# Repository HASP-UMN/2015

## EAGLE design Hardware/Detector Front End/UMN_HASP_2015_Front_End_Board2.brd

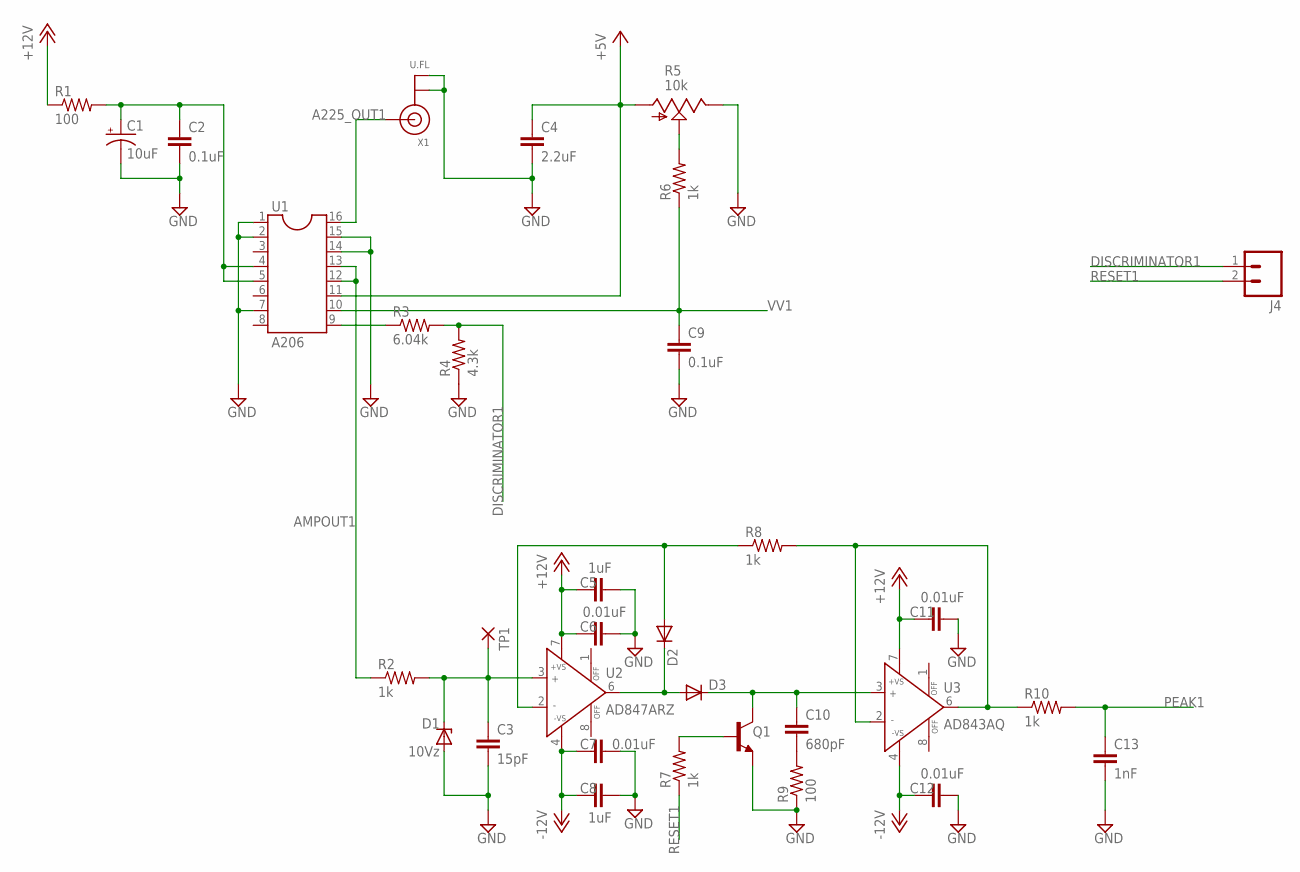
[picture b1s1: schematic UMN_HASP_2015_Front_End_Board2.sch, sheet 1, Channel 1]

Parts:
C1: 10uF; C/6032-28R
C2, C9: 0.1uF; C0603K
C3: 15pF; C0402K
C4: 2.2uF; C0603K
C5, C8: 1uF; C0603K
C6, C7, C11, C12: 0.01uF; C0402K
C10: 680pF; C0402K
C13: 1nF; C0402K
D1: 10Vz; SOT23
D2, D3: DIODE-SOD323-R; SOD323-R
J4: M02PTH; 1X02
Q1: -NPN-SOT23-EBC; SOT23-EBC
R1, R9: 100; R0603
R2, R6, R7, R8: 1k; R0603
R3: 6.04k; R0603
R4: 4.3k; R0603
R5: 10k; 3223J
R10: 1k; R0402
TP1: SMD2; SMD1,27-2,54
U1: A206; SOCKET-16
U2: AD847ARZ; SO8
U3: AD843AQ; DIL08
X1: U.FL

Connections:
+5V: C4.1, R5.1 (A), U1.11; also elsewhere on the board
+12V: C5.1, C6.1, C11.1, R1.1, U2.7 (+VS), U3.7 (+VS); also elsewhere on the board
-12V: C7.1, C8.1, C12.1, U2.4 (-VS), U3.4 (-VS); also elsewhere on the board
A225_OUT1: U1.16, X1.3 (SIGNAL)
AMPOUT1: R2.1, U1.12, U1.13
DISCRIMINATOR1: J4.1, R3.2, R4.2
GND: C1.-, C2.2, C3.2, C4.2, C5.2, C6.2, C7.2, C8.2, C9.2, C11.2, C12.2, C13.2, D1.1 (A), Q1.E, R4.1, R5.3 (E), R9.1, U1.1, U1.2, U1.7, U1.14, U1.15, X1.1 (GND), X1.2 (GND); also elsewhere on the board
unnamed: C1.+, C2.1, R1.2, U1.4, U1.5
unnamed: C3.1, D1.3 (C), R2.2, TP1.1, U2.3 (IN+)
unnamed: R3.1, U1.9
unnamed: D2.C, D3.A, U2.6 (OUT)
unnamed: R5.2 (S), R6.2
unnamed: D2.A, R8.1, U2.2 (IN-)
unnamed: C10.1, D3.C, Q1.C, U3.3 (IN+)
unnamed: C10.2, R9.2
unnamed: Q1.B, R7.2
unnamed: R8.2, R10.1, U3.2 (IN-), U3.6 (OUT)
PEAK1: C13.1, R10.2; also elsewhere on the board
RESET1: J4.2, R7.1
VV1: C9.1, R6.1, U1.10

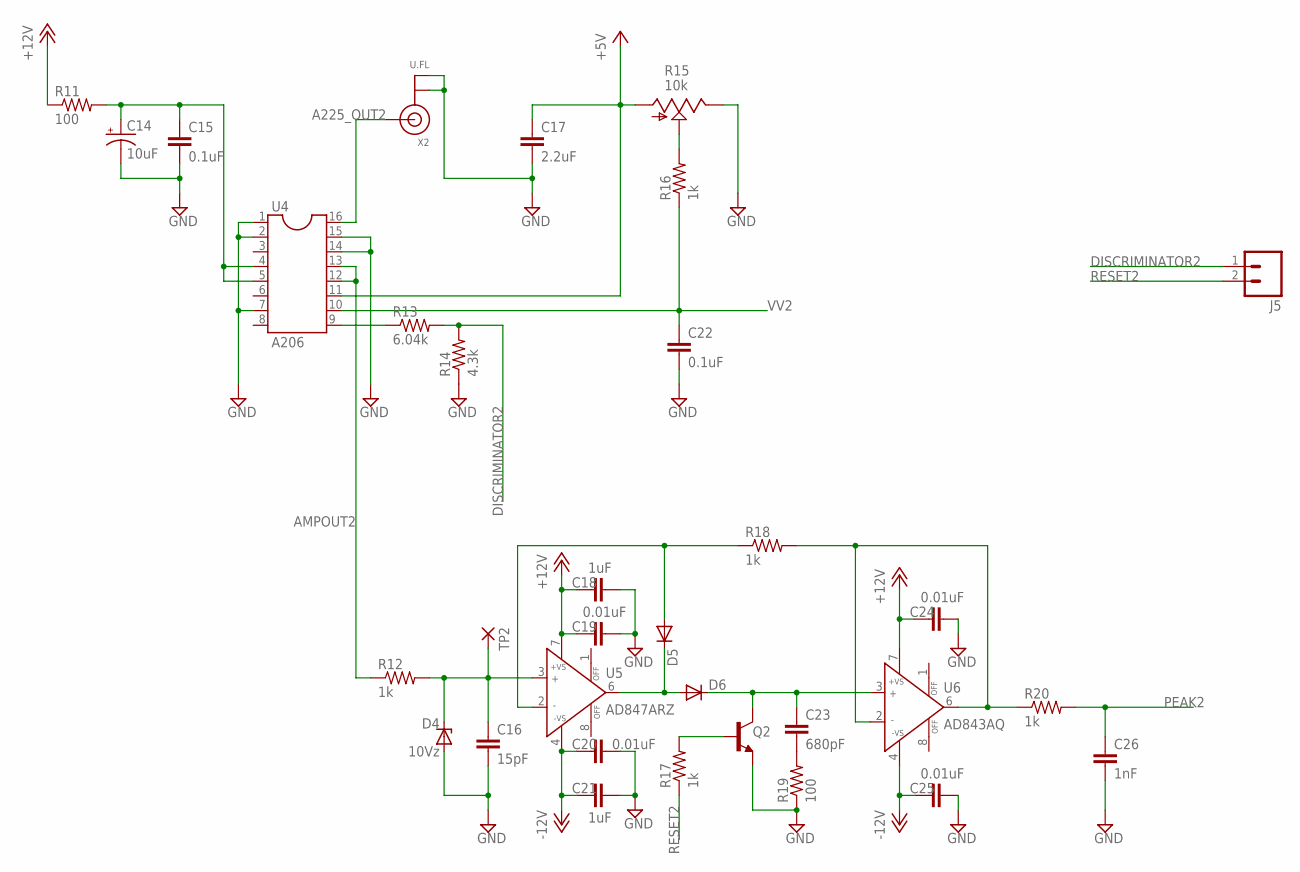
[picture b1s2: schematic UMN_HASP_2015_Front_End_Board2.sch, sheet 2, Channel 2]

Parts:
C14: 10uF; C/6032-28R
C15, C22: 0.1uF; C0603K
C16: 15pF; C0402K
C17: 2.2uF; C0603K
C18, C21: 1uF; C0603K
C19, C20, C24, C25: 0.01uF; C0402K
C23: 680pF; C0402K
C26: 1nF; C0402K
D4: 10Vz; SOT23
D5, D6: DIODE-SOD323-R; SOD323-R
J5: M02PTH; 1X02
Q2: -NPN-SOT23-EBC; SOT23-EBC
R11, R19: 100; R0603
R12, R16, R17, R18: 1k; R0603
R13: 6.04k; R0603
R14: 4.3k; R0603
R15: 10k; 3223J
R20: 1k; R0402
TP2: SMD2; SMD1,27-2,54
U4: A206; SOCKET-16
U5: AD847ARZ; SO8
U6: AD843AQ; DIL08
X2: U.FL

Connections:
+5V: C17.1, R15.1 (A), U4.11; also elsewhere on the board
+12V: C18.1, C19.1, C24.1, R11.1, U5.7 (+VS), U6.7 (+VS); also elsewhere on the board
-12V: C20.1, C21.1, C25.1, U5.4 (-VS), U6.4 (-VS); also elsewhere on the board
A225_OUT2: U4.16, X2.3 (SIGNAL)
AMPOUT2: R12.1, U4.12, U4.13
DISCRIMINATOR2: J5.1, R13.2, R14.2
GND: C14.-, C15.2, C16.2, C17.2, C18.2, C19.2, C20.2, C21.2, C22.2, C24.2, C25.2, C26.2, D4.1 (A), Q2.E, R14.1, R15.3 (E), R19.1, U4.1, U4.2, U4.7, U4.14, U4.15, X2.1 (GND), X2.2 (GND); also elsewhere on the board
unnamed: C14.+, C15.1, R11.2, U4.4, U4.5
unnamed: R13.1, U4.9
unnamed: R15.2 (S), R16.2
unnamed: C16.1, D4.3 (C), R12.2, TP2.1, U5.3 (IN+)
unnamed: D5.C, D6.A, U5.6 (OUT)
unnamed: D5.A, R18.1, U5.2 (IN-)
unnamed: C23.1, D6.C, Q2.C, U6.3 (IN+)
unnamed: C23.2, R19.2
unnamed: Q2.B, R17.2
unnamed: R18.2, R20.1, U6.2 (IN-), U6.6 (OUT)
PEAK2: C26.1, R20.2; also elsewhere on the board
RESET2: J5.2, R17.1
VV2: C22.1, R16.1, U4.10

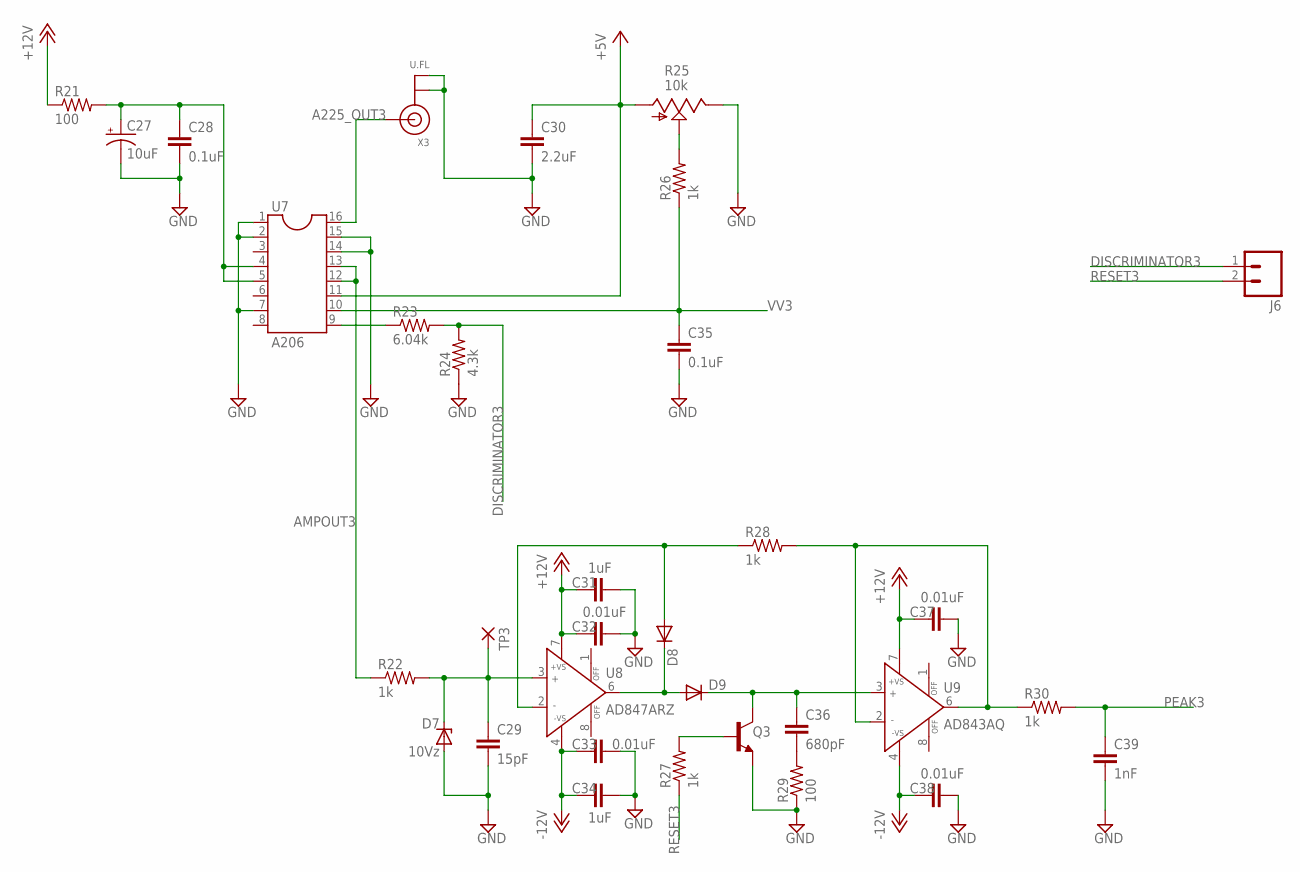
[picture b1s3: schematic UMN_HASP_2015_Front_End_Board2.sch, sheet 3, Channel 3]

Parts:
C27: 10uF; C/6032-28R
C28, C35: 0.1uF; C0603K
C29: 15pF; C0402K
C30: 2.2uF; C0603K
C31, C34: 1uF; C0603K
C32, C33, C37, C38: 0.01uF; C0402K
C36: 680pF; C0402K
C39: 1nF; C0402K
D7: 10Vz; SOT23
D8, D9: DIODE-SOD323-R; SOD323-R
J6: M02PTH; 1X02
Q3: -NPN-SOT23-EBC; SOT23-EBC
R21, R29: 100; R0603
R22, R26, R27, R28: 1k; R0603
R23: 6.04k; R0603
R24: 4.3k; R0603
R25: 10k; 3223J
R30: 1k; R0402
TP3: SMD2; SMD1,27-2,54
U7: A206; SOCKET-16
U8: AD847ARZ; SO8
U9: AD843AQ; DIL08
X3: U.FL

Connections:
+5V: C30.1, R25.1 (A), U7.11; also elsewhere on the board
+12V: C31.1, C32.1, C37.1, R21.1, U8.7 (+VS), U9.7 (+VS); also elsewhere on the board
-12V: C33.1, C34.1, C38.1, U8.4 (-VS), U9.4 (-VS); also elsewhere on the board
A225_OUT3: U7.16, X3.3 (SIGNAL)
AMPOUT3: R22.1, U7.12, U7.13
DISCRIMINATOR3: J6.1, R23.2, R24.2
GND: C27.-, C28.2, C29.2, C30.2, C31.2, C32.2, C33.2, C34.2, C35.2, C37.2, C38.2, C39.2, D7.1 (A), Q3.E, R24.1, R25.3 (E), R29.1, U7.1, U7.2, U7.7, U7.14, U7.15, X3.1 (GND), X3.2 (GND); also elsewhere on the board
unnamed: C27.+, C28.1, R21.2, U7.4, U7.5
unnamed: R23.1, U7.9
unnamed: R25.2 (S), R26.2
unnamed: C29.1, D7.3 (C), R22.2, TP3.1, U8.3 (IN+)
unnamed: D8.C, D9.A, U8.6 (OUT)
unnamed: D8.A, R28.1, U8.2 (IN-)
unnamed: C36.1, D9.C, Q3.C, U9.3 (IN+)
unnamed: C36.2, R29.2
unnamed: Q3.B, R27.2
unnamed: R28.2, R30.1, U9.2 (IN-), U9.6 (OUT)
PEAK3: C39.1, R30.2; also elsewhere on the board
RESET3: J6.2, R27.1
VV3: C35.1, R26.1, U7.10

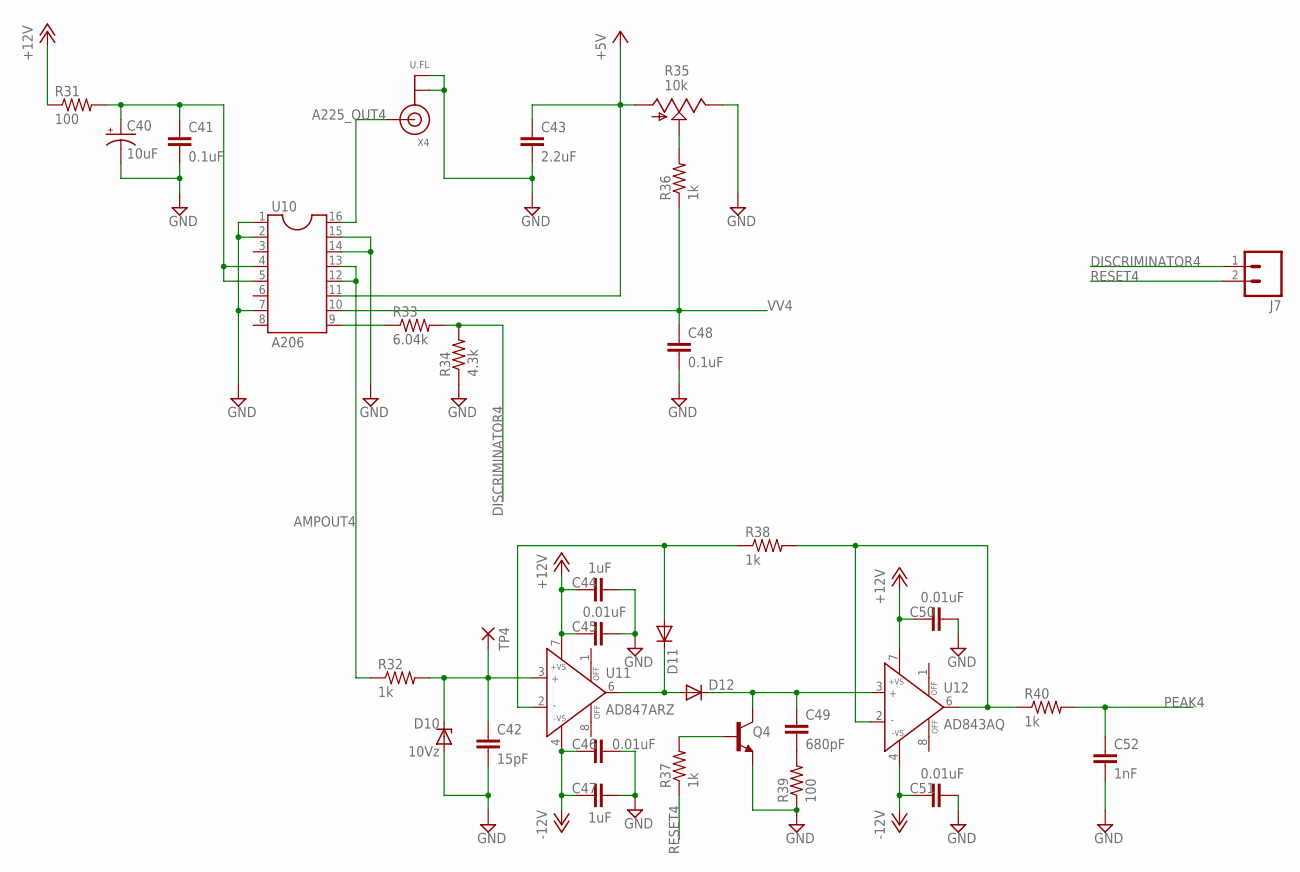
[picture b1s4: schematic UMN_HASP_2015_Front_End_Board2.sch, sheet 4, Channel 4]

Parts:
C40: 10uF; C/6032-28R
C41, C48: 0.1uF; C0603K
C42: 15pF; C0402K
C43: 2.2uF; C0603K
C44, C47: 1uF; C0603K
C45, C46, C50, C51: 0.01uF; C0402K
C49: 680pF; C0402K
C52: 1nF; C0402K
D10: 10Vz; SOT23
D11, D12: DIODE-SOD323-R; SOD323-R
J7: M02PTH; 1X02
Q4: -NPN-SOT23-EBC; SOT23-EBC
R31, R39: 100; R0603
R32, R36, R37, R38: 1k; R0603
R33: 6.04k; R0603
R34: 4.3k; R0603
R35: 10k; 3223J
R40: 1k; R0402
TP4: SMD2; SMD1,27-2,54
U10: A206; SOCKET-16
U11: AD847ARZ; SO8
U12: AD843AQ; DIL08
X4: U.FL

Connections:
+5V: C43.1, R35.1 (A), U10.11; also elsewhere on the board
+12V: C44.1, C45.1, C50.1, R31.1, U11.7 (+VS), U12.7 (+VS); also elsewhere on the board
-12V: C46.1, C47.1, C51.1, U11.4 (-VS), U12.4 (-VS); also elsewhere on the board
A225_OUT4: U10.16, X4.3 (SIGNAL)
AMPOUT4: R32.1, U10.12, U10.13
DISCRIMINATOR4: J7.1, R33.2, R34.2
GND: C40.-, C41.2, C42.2, C43.2, C44.2, C45.2, C46.2, C47.2, C48.2, C50.2, C51.2, C52.2, D10.1 (A), Q4.E, R34.1, R35.3 (E), R39.1, U10.1, U10.2, U10.7, U10.14, U10.15, X4.1 (GND), X4.2 (GND); also elsewhere on the board
unnamed: C40.+, C41.1, R31.2, U10.4, U10.5
unnamed: R33.1, U10.9
unnamed: R35.2 (S), R36.2
unnamed: C42.1, D10.3 (C), R32.2, TP4.1, U11.3 (IN+)
unnamed: D11.C, D12.A, U11.6 (OUT)
unnamed: D11.A, R38.1, U11.2 (IN-)
unnamed: C49.1, D12.C, Q4.C, U12.3 (IN+)
unnamed: C49.2, R39.2
unnamed: Q4.B, R37.2
unnamed: R38.2, R40.1, U12.2 (IN-), U12.6 (OUT)
PEAK4: C52.1, R40.2; also elsewhere on the board
RESET4: J7.2, R37.1
VV4: C48.1, R36.1, U10.10

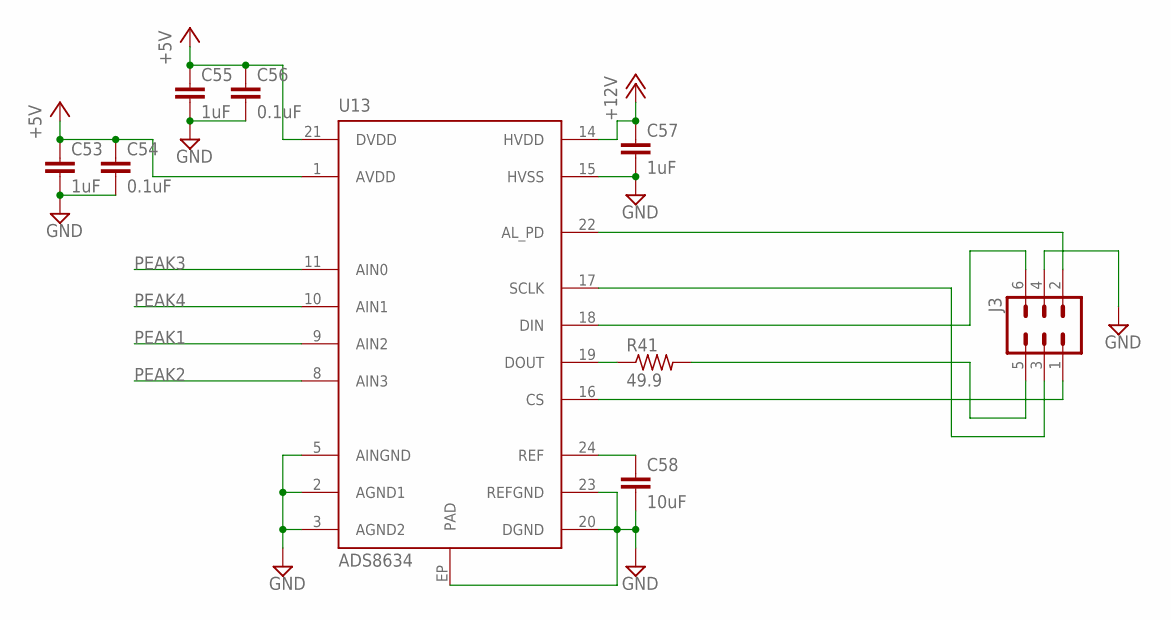
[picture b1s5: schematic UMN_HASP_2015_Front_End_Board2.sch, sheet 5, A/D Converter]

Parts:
C53, C55, C57: 1uF; C0402K
C54, C56: 0.1uF; C0402K
C58: 10uF; C0603K
J3: MA03-2
R41: 49.9; R0402
U13: ADS8634; QFN24

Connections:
+5V: C53.1, C54.1, C55.1, C56.1, U13.1 (AVDD), U13.21 (DVDD); also elsewhere on the board
+12V: C57.1, U13.14 (HVDD); also elsewhere on the board
AL_PD: J3.2, U13.22 (AL_PD)
CS: J3.1, U13.16 (CS)
DIN: J3.6, U13.18 (DIN)
DOUT: J3.5, R41.2
GND: C53.2, C54.2, C55.2, C56.2, C57.2, C58.2, J3.4, U13.2 (AGND1), U13.3 (AGND2), U13.5 (AINGND), U13.15 (HVSS), U13.20 (DGND), U13.23 (REFGND), U13.EP (PAD); also elsewhere on the board
unnamed: R41.1, U13.19 (DOUT)
PEAK1: U13.9 (AIN2); also elsewhere on the board
PEAK2: U13.8 (AIN3); also elsewhere on the board
PEAK3: U13.11 (AIN0); also elsewhere on the board
PEAK4: U13.10 (AIN1); also elsewhere on the board
REF: C58.1, U13.24 (REF)
SCLK: J3.3, U13.17 (SCLK)

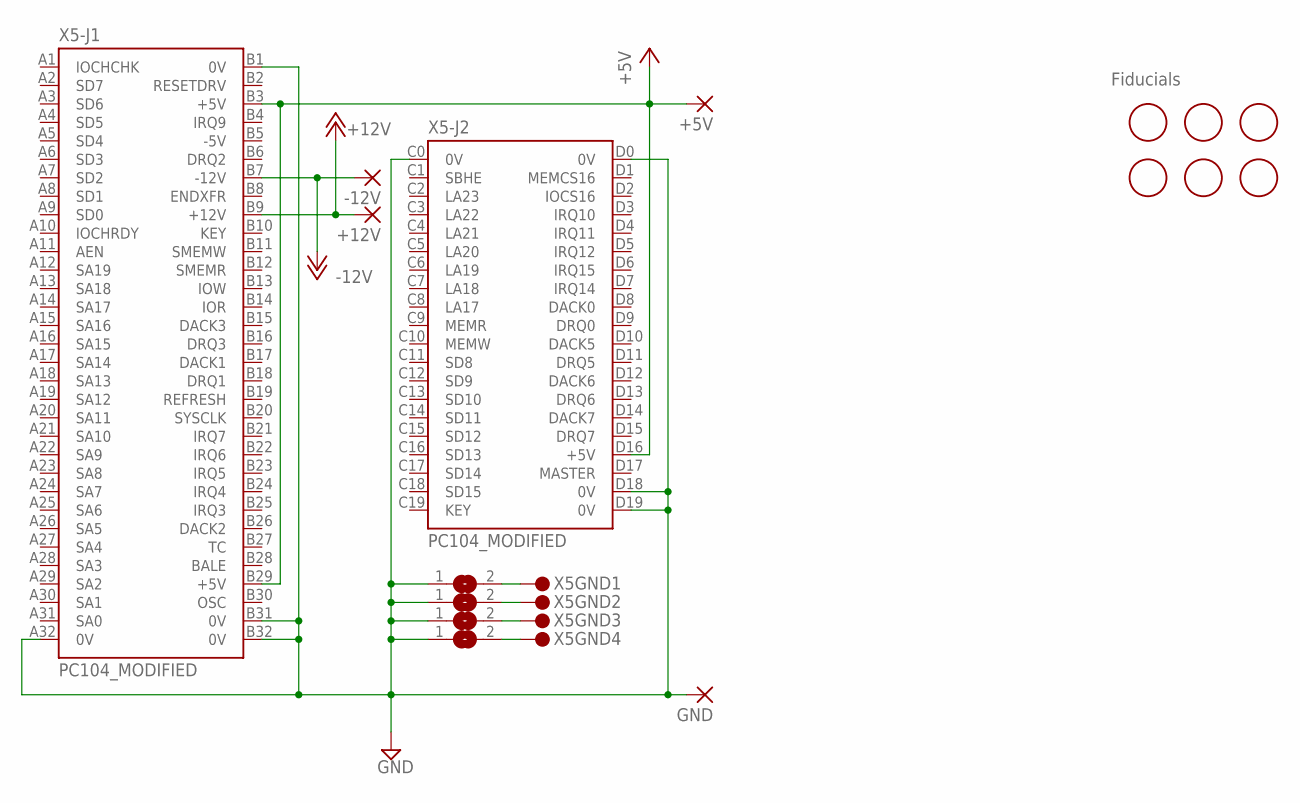
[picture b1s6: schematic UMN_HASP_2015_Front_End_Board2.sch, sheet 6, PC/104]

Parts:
+5V, +12V: SMD2; SMD1,27-2,54
-12V: SMD2; SMD1,27-2,54
F1, F2, F3, F4, F5, F6: FIDUCIAL; FIDUCIAL_1MM
GND: SMD2; SMD1,27-2,54
SJ1, SJ2, SJ3, SJ4: SJ
X5: PC104_MODIFIED

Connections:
+5V: +5V.1, X5.B3 (+5V), X5.B29 (+5V), X5.D16 (+5V); also elsewhere on the board
+12V: +12V.1, X5.B9 (+12V); also elsewhere on the board
-12V: -12V.1, X5.B7 (-12V); also elsewhere on the board
GND: GND.1, SJ1.1, SJ2.1, SJ3.1, SJ4.1, X5.A32 (0V), X5.B1 (0V), X5.B31 (0V), X5.B32 (0V), X5.C0 (0V), X5.D0 (0V), X5.D18 (0V), X5.D19 (0V); also elsewhere on the board
unnamed: SJ1.2, X5.GND@1 (1)
unnamed: SJ2.2, X5.GND@2 (1)
unnamed: SJ3.2, X5.GND@3 (1)
unnamed: SJ4.2, X5.GND@4 (1)

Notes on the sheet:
Fiducials

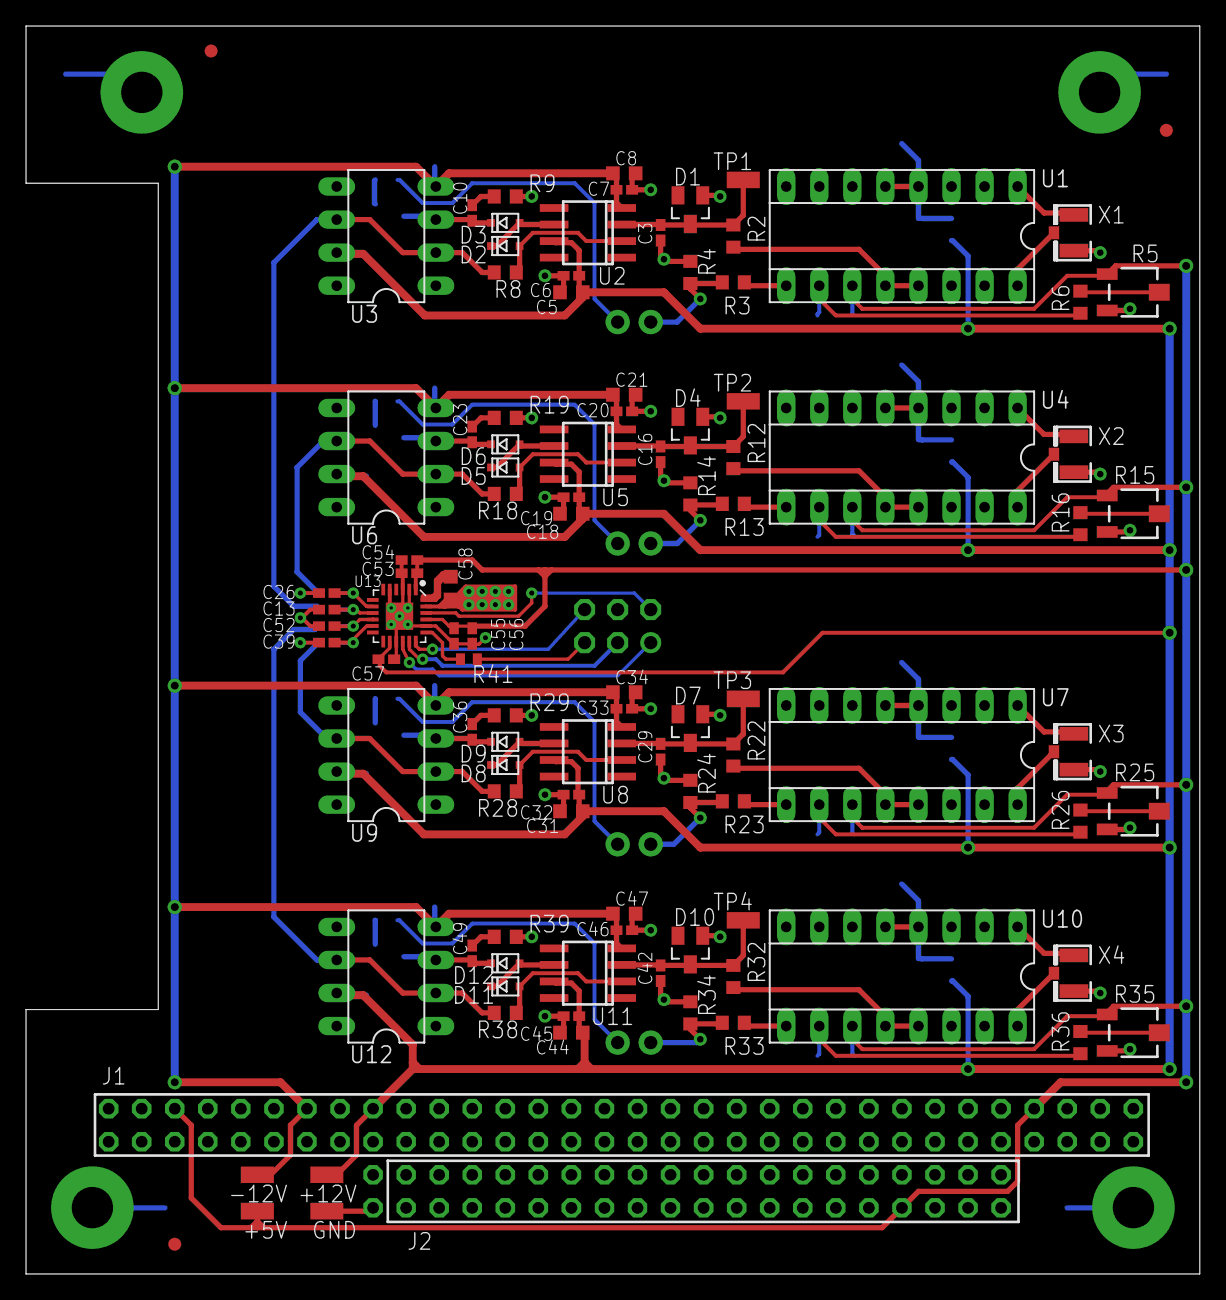
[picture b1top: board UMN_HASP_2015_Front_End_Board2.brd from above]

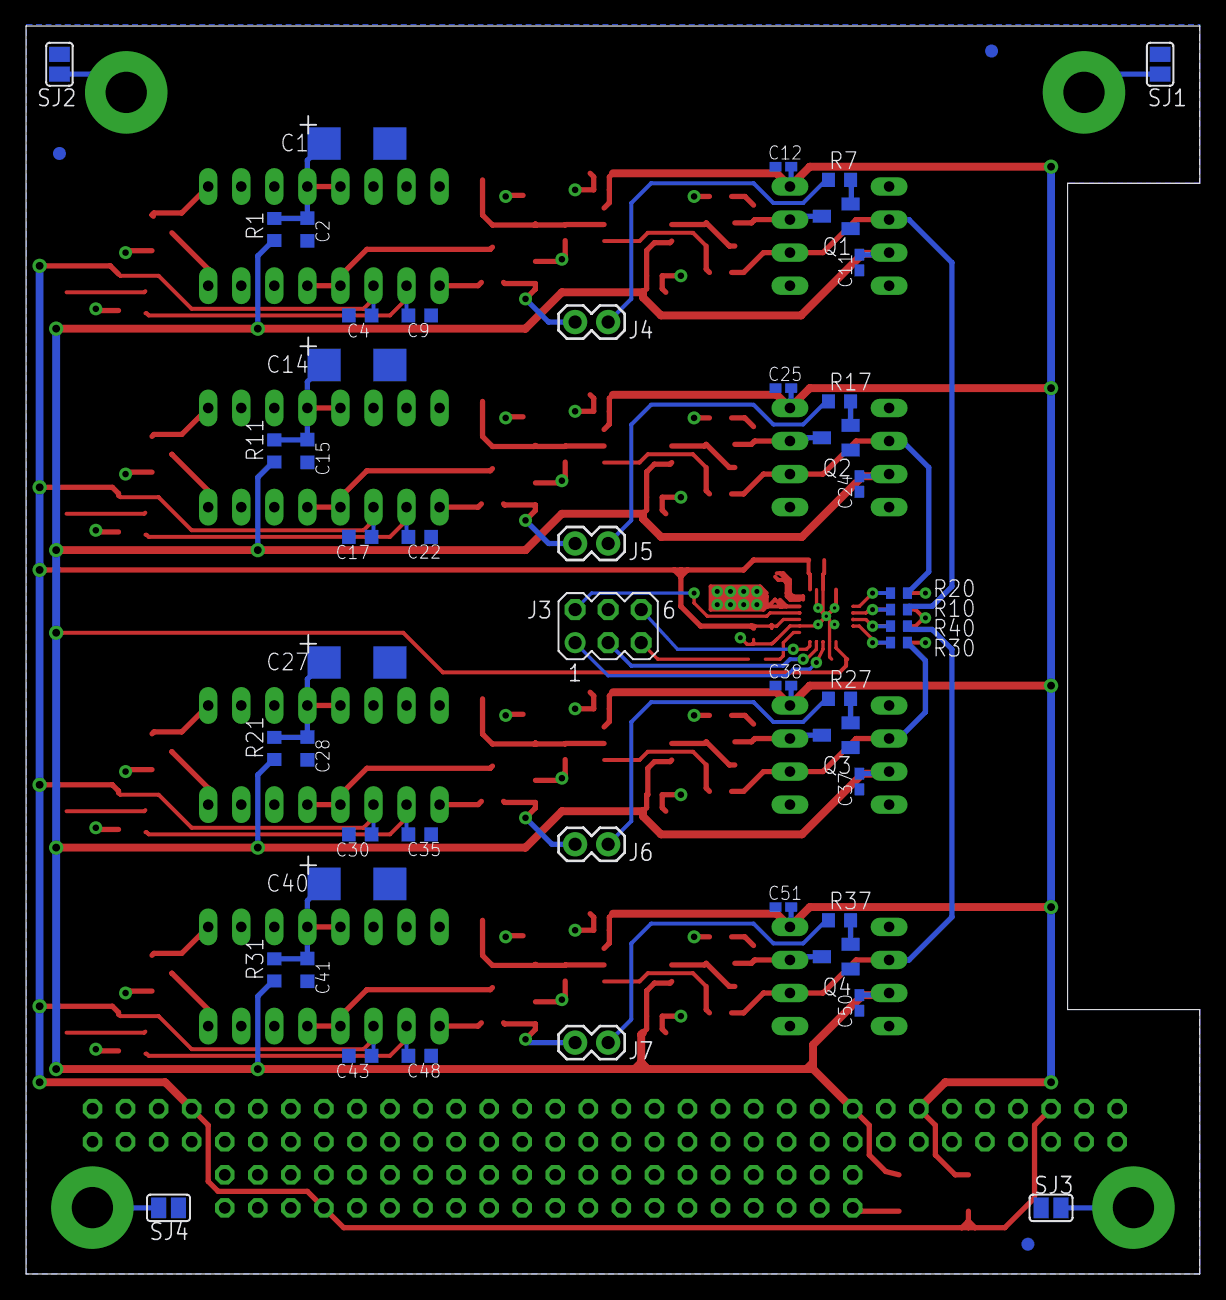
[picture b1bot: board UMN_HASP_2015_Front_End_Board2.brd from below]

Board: 2 copper layers, 90.2 x 95.9 mm, 156 parts (52 on the bottom side), 79 nets.

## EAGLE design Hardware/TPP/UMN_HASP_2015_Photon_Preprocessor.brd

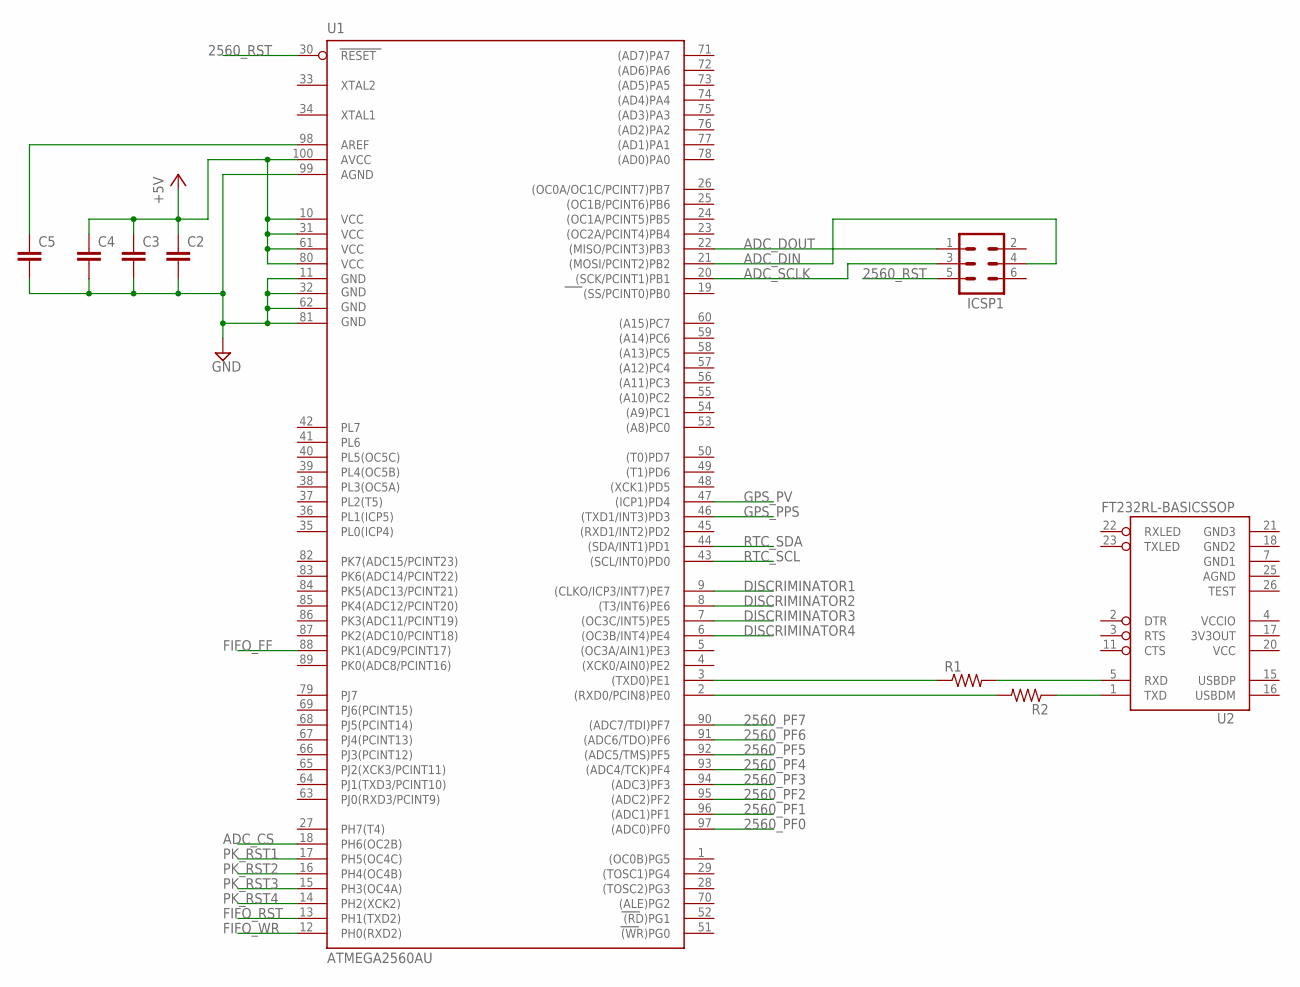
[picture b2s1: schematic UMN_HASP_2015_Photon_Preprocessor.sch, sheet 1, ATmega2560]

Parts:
C2, C3, C4, C5: C-EUC0603K; C0603K
ICSP1: MA03-2
R1, R2: R-US_R0603; R0603
U1: ATMEGA2560AU; TQFP100
U2: FT232RL-BASICSSOP; SSOP28DB

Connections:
2560_PF0: U1.97 ((ADC0)PF0); also elsewhere on the board
2560_PF1: U1.96 ((ADC1)PF1); also elsewhere on the board
2560_PF2: U1.95 ((ADC2)PF2); also elsewhere on the board
2560_PF3: U1.94 ((ADC3)PF3); also elsewhere on the board
2560_PF4: U1.93 ((ADC4/TCK)PF4); also elsewhere on the board
2560_PF5: U1.92 ((ADC5/TMS)PF5); also elsewhere on the board
2560_PF6: U1.91 ((ADC6/TDO)PF6); also elsewhere on the board
2560_PF7: U1.90 ((ADC7/TDI)PF7); also elsewhere on the board
2560_RST: ICSP1.5, U1.30 (RESET)
+5V: C2.1, C3.1, C4.1, U1.10 (VCC), U1.31 (VCC1), U1.61 (VCC2), U1.80 (VCC3), U1.100 (AVCC); also elsewhere on the board
ADC_CS: U1.18 (PH6(OC2B)); also elsewhere on the board
ADC_DIN: ICSP1.4, U1.21 ((MOSI/PCINT2)PB2); also elsewhere on the board
ADC_DOUT: ICSP1.1, U1.22 ((MISO/PCINT3)PB3); also elsewhere on the board
ADC_SCLK: ICSP1.3, U1.20 ((SCK/PCINT1)PB1); also elsewhere on the board
AGND: U2.25 (AGND)
DISCRIMINATOR1: U1.9 ((CLKO/ICP3/INT7)PE7); also elsewhere on the board
DISCRIMINATOR2: U1.8 ((T3/INT6)PE6); also elsewhere on the board
DISCRIMINATOR3: U1.7 ((OC3C/INT5)PE5); also elsewhere on the board
DISCRIMINATOR4: U1.6 ((OC3B/INT4)PE4); also elsewhere on the board
FIFO_FF: U1.88 (PK1(ADC9/PCINT17)); also elsewhere on the board
FIFO_RST: U1.13 (PH1(TXD2)); also elsewhere on the board
FIFO_WR: U1.12 (PH0(RXD2)); also elsewhere on the board
GND: C2.2, C3.2, C4.2, C5.2, U1.11 (GND), U1.32 (GND1), U1.62 (GND2), U1.81 (GND3), U1.99 (AGND); also elsewhere on the board
GND1: U2.7 (GND1)
GND2: U2.18 (GND2)
GND3: U2.21 (GND3)
GPS_PPS: U1.46 ((TXD1/INT3)PD3); also elsewhere on the board
GPS_PV: U1.47 ((ICP1)PD4); also elsewhere on the board
unnamed: R2.1, U2.1 (TXD)
unnamed: R1.2, U2.5 (RXD)
unnamed: C5.1, U1.98 (AREF)
unnamed: R2.2, U1.2 ((RXD0/PCIN8)PE0)
unnamed: R1.1, U1.3 ((TXD0)PE1)
PK_RST1: U1.17 (PH5(OC4C)); also elsewhere on the board
PK_RST2: U1.16 (PH4(OC4B)); also elsewhere on the board
PK_RST3: U1.15 (PH3(OC4A)); also elsewhere on the board
PK_RST4: U1.14 (PH2(XCK2)); also elsewhere on the board
RTC_SCL: U1.43 ((SCL/INT0)PD0); also elsewhere on the board
RTC_SDA: U1.44 ((SDA/INT1)PD1); also elsewhere on the board
VCC: U2.20 (VCC); also elsewhere on the board
VCCIO: U2.4 (VCCIO)

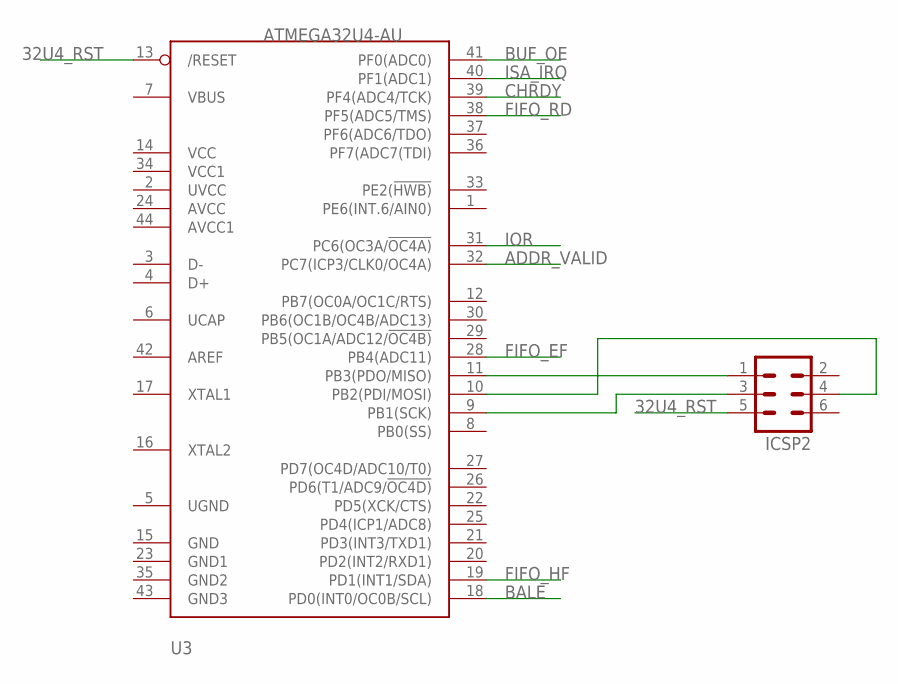
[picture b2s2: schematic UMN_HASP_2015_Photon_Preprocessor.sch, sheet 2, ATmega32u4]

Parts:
ICSP2: MA03-2
U3: ATMEGA32U4-AU; TQFP44

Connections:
32U4_RST: ICSP2.5, U3.13 (/RESET)
ADDR_VALID: U3.32 (PC7(ICP3/CLK0/OC4A)); also elsewhere on the board
BALE: U3.18 (PD0(INT0/OC0B/SCL)); also elsewhere on the board
BUF_OE: U3.41 (PF0(ADC0)); also elsewhere on the board
CHRDY: U3.39 (PF4(ADC4/TCK)); also elsewhere on the board
FIFO_EF: U3.28 (PB4(ADC11)); also elsewhere on the board
FIFO_HF: U3.19 (PD1(INT1/SDA)); also elsewhere on the board
FIFO_RD: U3.38 (PF5(ADC5/TMS)); also elsewhere on the board
IOR: U3.31 (PC6(OC3A/!OC4A)); also elsewhere on the board
ISA_IRQ: U3.40 (PF1(ADC1)); also elsewhere on the board
unnamed: ICSP2.1, U3.11 (PB3(PDO/MISO))
unnamed: ICSP2.3, U3.9 (PB1(SCK))
unnamed: ICSP2.4, U3.10 (PB2(PDI/MOSI))

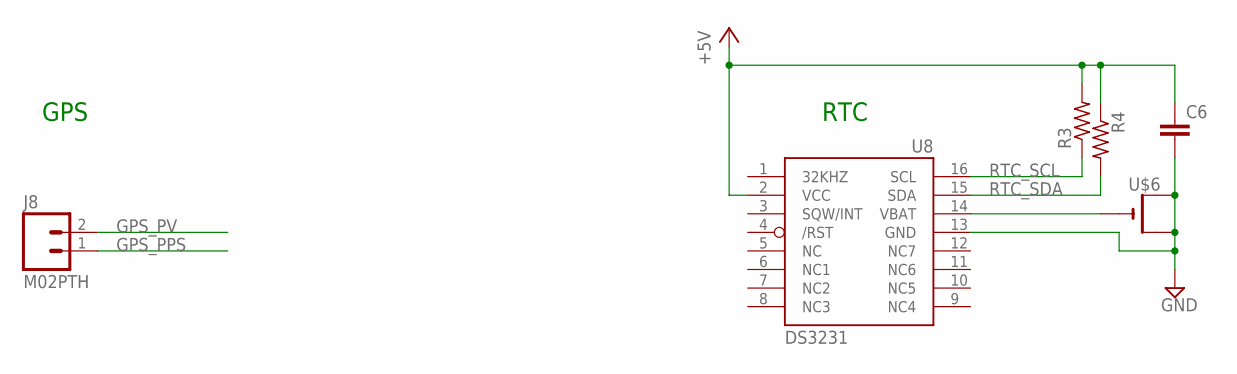
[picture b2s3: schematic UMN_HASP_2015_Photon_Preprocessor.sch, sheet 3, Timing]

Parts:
C6: C-EUC0603K; C0603K
J8: M02PTH; 1X02
R3, R4: R-US_R0603; R0603
U8: DS3231/SO; SO16W
U$6: CR1220SMT; CR1220-SMD

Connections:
+5V: C6.1, R3.2, R4.1, U8.2 (VCC); also elsewhere on the board
GND: C6.2, U8.13 (GND), U$6.+$1 (+), U$6.+$2 (+1); also elsewhere on the board
GPS_PPS: J8.1; also elsewhere on the board
GPS_PV: J8.2; also elsewhere on the board
unnamed: U8.14 (VBAT), U$6.-
RTC_SCL: R3.1, U8.16 (SCL); also elsewhere on the board
RTC_SDA: R4.2, U8.15 (SDA); also elsewhere on the board

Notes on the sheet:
GPS
RTC

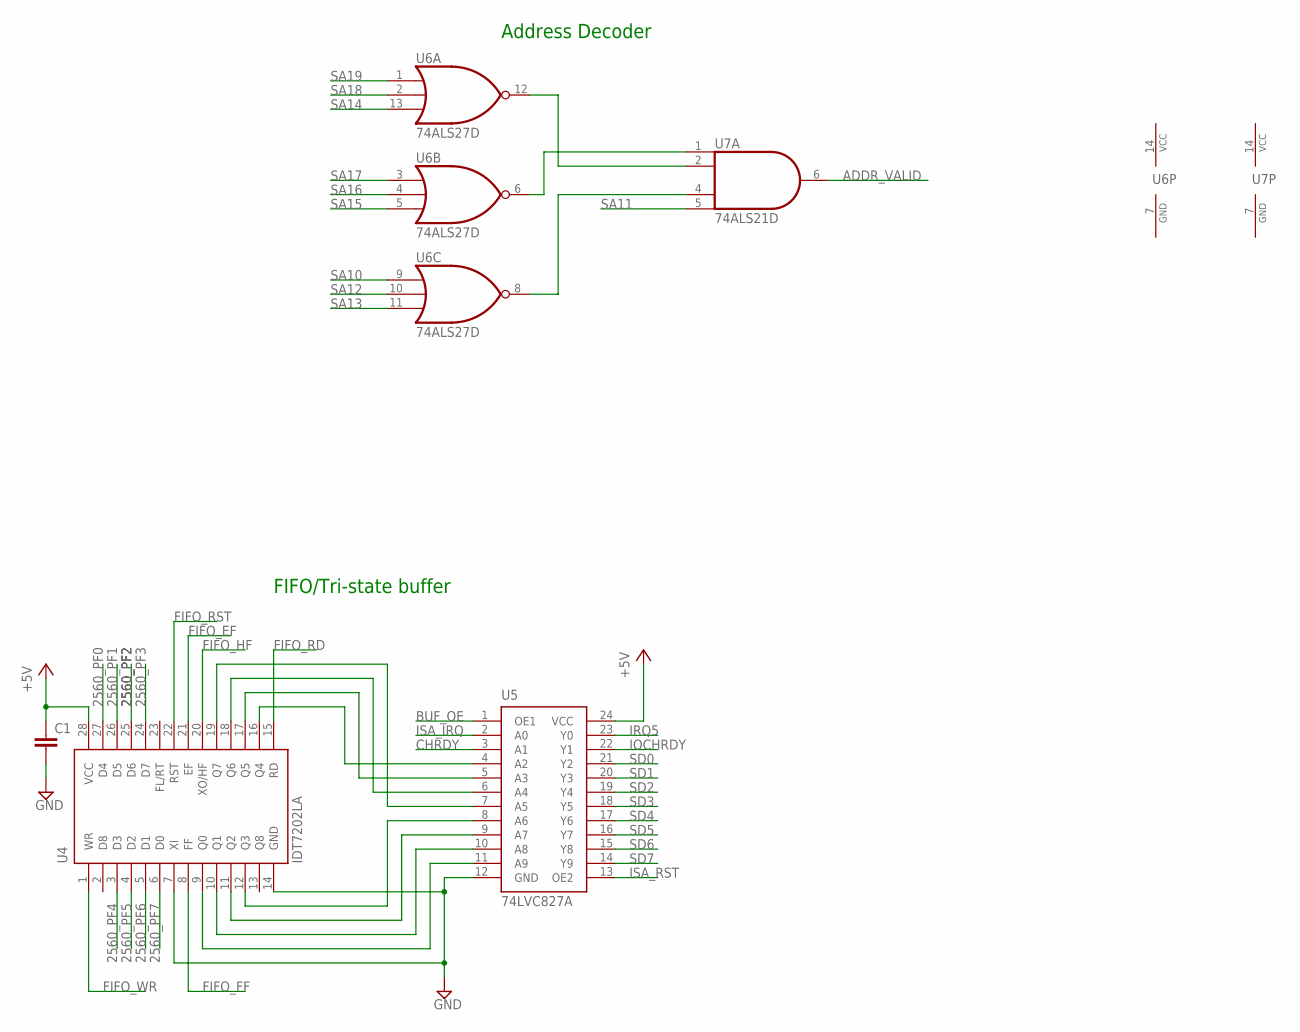
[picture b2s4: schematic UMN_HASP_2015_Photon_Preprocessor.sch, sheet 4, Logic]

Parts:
C1: C-EUC0603K; C0603K
U4: IDT7202LA; SO28W
U5: 74LVC827A; SO24W
U6: 74ALS27D; SO14
U7: 74ALS21D; SO14

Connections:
2560_PF0: U4.27 (D4); also elsewhere on the board
2560_PF1: U4.26 (D5); also elsewhere on the board
2560_PF2: U4.25 (D6); also elsewhere on the board
2560_PF3: U4.24 (D7); also elsewhere on the board
2560_PF4: U4.3 (D3); also elsewhere on the board
2560_PF5: U4.4 (D2); also elsewhere on the board
2560_PF6: U4.5 (D1); also elsewhere on the board
2560_PF7: U4.6 (D0); also elsewhere on the board
+5V: C1.1, U4.28 (VCC), U5.24 (VCC); also elsewhere on the board
ADDR_VALID: U7.6 (O); also elsewhere on the board
BUF_OE: U5.1 (OE1); also elsewhere on the board
CHRDY: U5.3 (A1); also elsewhere on the board
FIFO_EF: U4.21 (EF); also elsewhere on the board
FIFO_FF: U4.8 (FF); also elsewhere on the board
FIFO_HF: U4.20 (XO/HF); also elsewhere on the board
FIFO_RD: U4.15 (RD); also elsewhere on the board
FIFO_RST: U4.22 (RST); also elsewhere on the board
FIFO_WR: U4.1 (WR); also elsewhere on the board
GND: C1.2, U4.7 (XI), U4.14 (GND), U5.12 (GND), U6.7 (GND), U7.7 (GND); also elsewhere on the board
IOCHRDY: U5.22 (Y1); also elsewhere on the board
IRQ5: U5.23 (Y0); also elsewhere on the board
ISA_IRQ: U5.2 (A0); also elsewhere on the board
ISA_RST: U5.13 (OE2); also elsewhere on the board
unnamed: U6.12 (O), U7.2 (I1)
unnamed: U6.6 (O), U7.1 (I0)
unnamed: U6.8 (O), U7.4 (I2)
unnamed: U4.12 (Q3), U5.8 (A6)
unnamed: U4.11 (Q2), U5.9 (A7)
unnamed: U4.10 (Q1), U5.10 (A8)
unnamed: U4.9 (Q0), U5.11 (A9)
unnamed: U4.16 (Q4), U5.4 (A2)
unnamed: U4.19 (Q7), U5.7 (A5)
unnamed: U4.18 (Q6), U5.6 (A4)
unnamed: U4.17 (Q5), U5.5 (A3)
SA10: U6.9 (I0); also elsewhere on the board
SA11: U7.5 (I3); also elsewhere on the board
SA12: U6.10 (I1); also elsewhere on the board
SA13: U6.11 (I2); also elsewhere on the board
SA14: U6.13 (I2); also elsewhere on the board
SA15: U6.5 (I2); also elsewhere on the board
SA16: U6.4 (I1); also elsewhere on the board
SA17: U6.3 (I0); also elsewhere on the board
SA18: U6.2 (I1); also elsewhere on the board
SA19: U6.1 (I0); also elsewhere on the board
SD0: U5.21 (Y2); also elsewhere on the board
SD1: U5.20 (Y3); also elsewhere on the board
SD2: U5.19 (Y4); also elsewhere on the board
SD3: U5.18 (Y5); also elsewhere on the board
SD4: U5.17 (Y6); also elsewhere on the board
SD5: U5.16 (Y7); also elsewhere on the board
SD6: U5.15 (Y8); also elsewhere on the board
SD7: U5.14 (Y9); also elsewhere on the board
VCC: U6.14 (VCC), U7.14 (VCC); also elsewhere on the board

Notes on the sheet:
Address Decoder
FIFO/Tri-state buffer

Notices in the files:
parts and their libraries:
con-pc104: Copyright 1992-96, PC/104 Consortium
Copyright 1992-98, PC/104 Consortium
SparkFun-Connectors: Licensing: Creative Commons ShareAlike 4.0 International - https://creativecommons.org/licenses/by-sa/4.0
